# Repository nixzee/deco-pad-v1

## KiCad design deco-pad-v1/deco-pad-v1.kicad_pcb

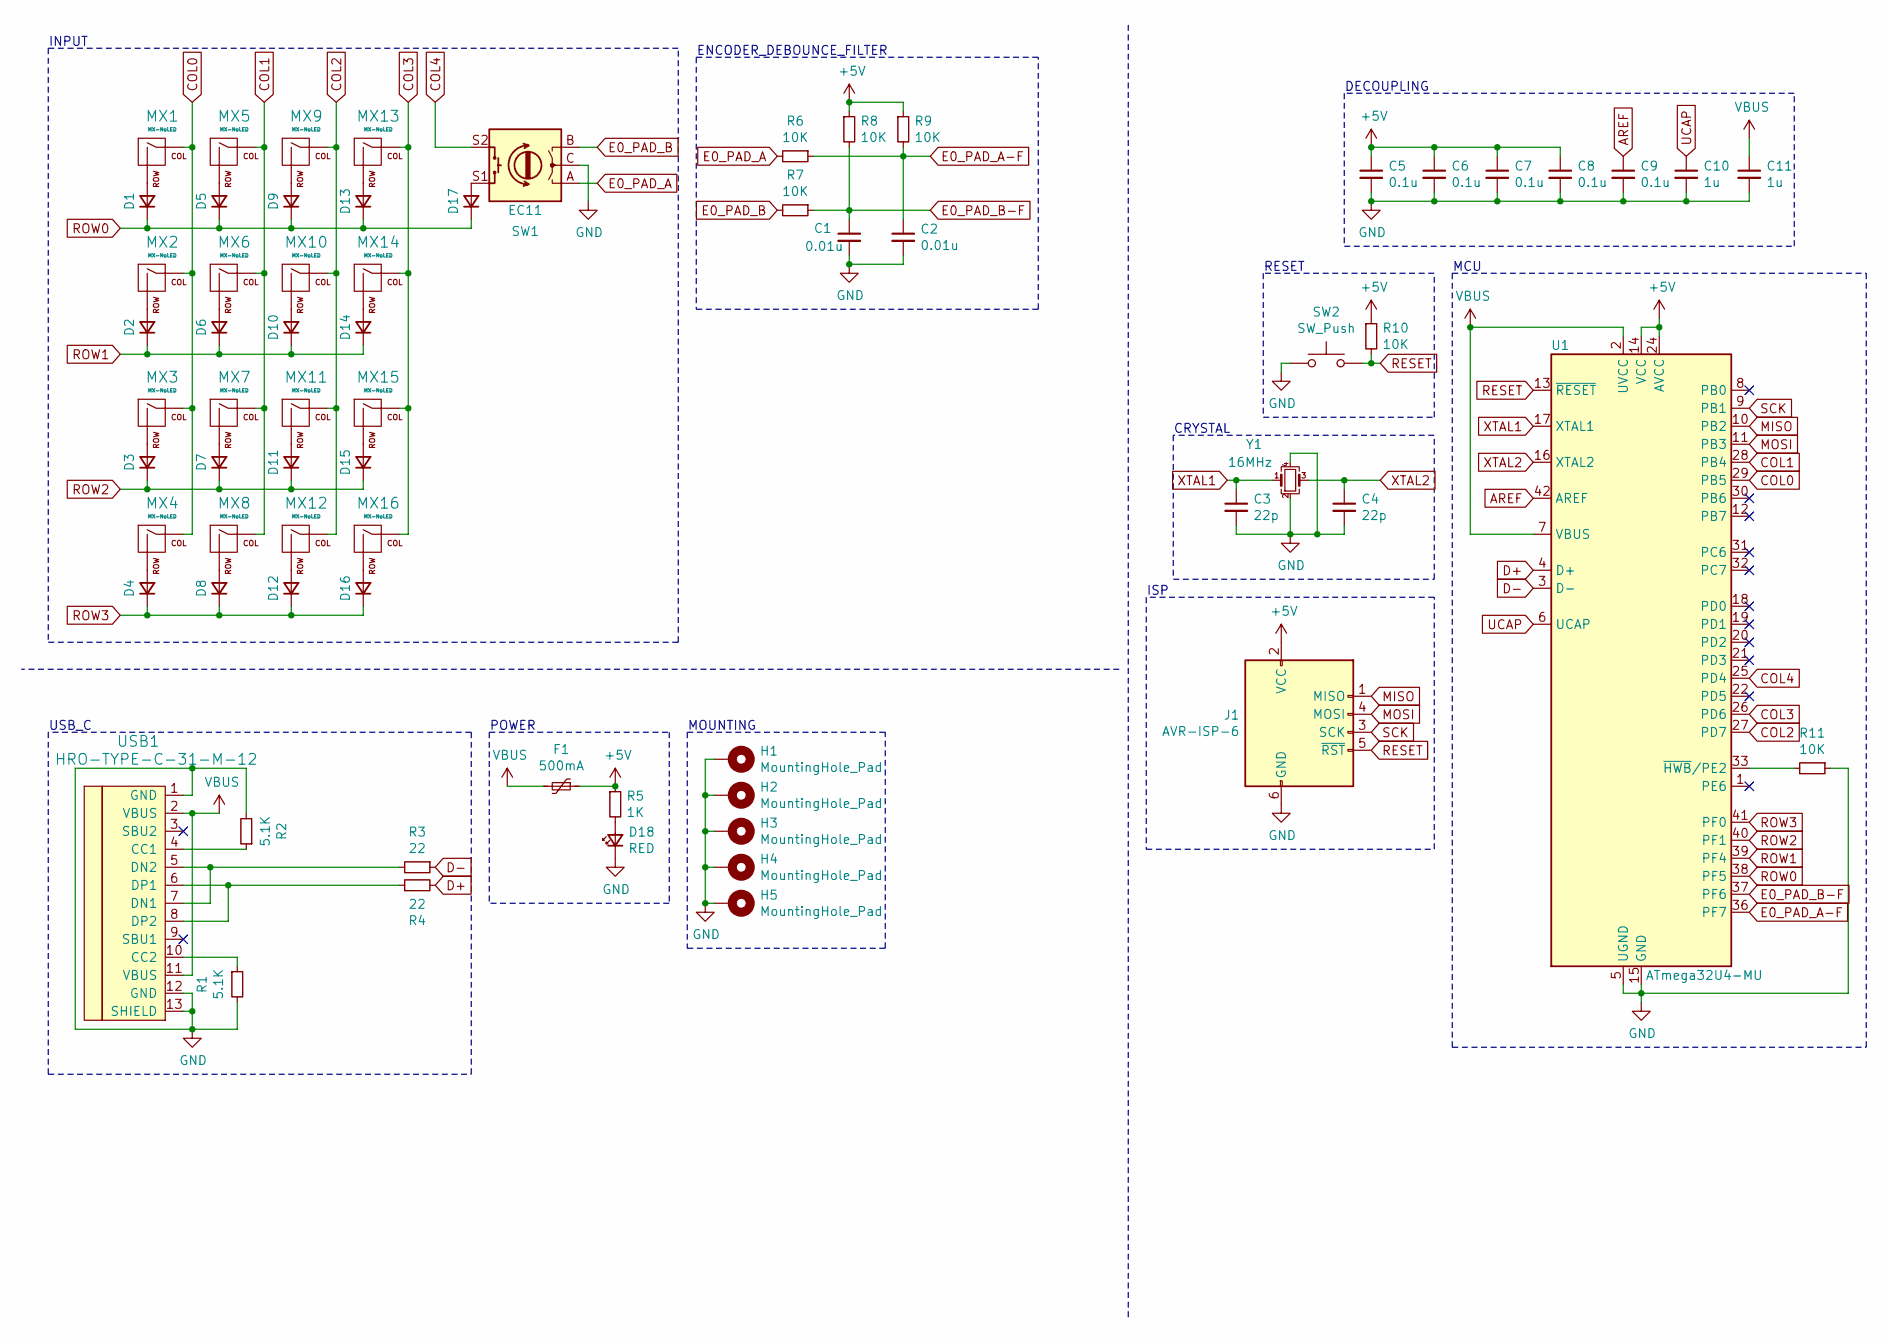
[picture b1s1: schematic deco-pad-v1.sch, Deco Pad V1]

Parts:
C1, C2: 0.01u; C_0805_2012Metric
C3, C4: 22p; C_0805_2012Metric
C5, C6, C7, C8, C9: 0.1u; C_0805_2012Metric
C10, C11: 1u; C_0805_2012Metric
D1, D2, D3, D4, D5, D6, D7, D8, D9, D10, D11, D12, D13, D14, D15, D16, D17: D_Small; D_SOD-123
D18: RED; LED_0805_2012Metric
F1: 500mA; Fuse_1206_3216Metric
H1, H2, H3, H4, H5: MountingHole_Pad; MountingHole_2.2mm_M2_Pad_Via
J1: AVR-ISP-6; PinSocket_2x03_P2.54mm_Vertical
MX1, MX2, MX3, MX4, MX5, MX6, MX7, MX8, MX9, MX10, MX11, MX12, MX13, MX14, MX15, MX16: MX-NoLED; MX-1U-NoLED
R1, R2: 5.1K; R_0805_2012Metric
R3, R4: 22; R_0805_2012Metric
R5: 1K; R_0805_2012Metric
R6, R7, R8, R9, R10, R11: 10K; R_0805_2012Metric
SW1: EC11; RotaryEncoder_Alps_EC11E-Switch_Vertical_H20mm
SW2: SW_Push; SW_SPST_B3S-1000
U1: ATmega32U4-MU; QFN-44-1EP_7x7mm_P0.5mm_EP5.2x5.2mm
USB1: HRO-TYPE-C-31-M-12; HRO-TYPE-C-31-M-12-HandSoldering
Y1: 16MHz; Crystal_SMD_3225-4Pin_3.2x2.5mm

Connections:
+5V: C5.1, C6.1, C7.1, C8.1, F1.1, J1.2 (VCC), R5.1, R8.1, R9.1, R10.1, U1.14 (VCC), U1.24 (AVCC), U1.34 (VCC), U1.44 (AVCC)
AREF: C9.1, U1.42 (AREF)
COL0: MX1.1 (COL), MX2.1 (COL), MX3.1 (COL), MX4.1 (COL), U1.29 (PB5)
COL1: MX5.1 (COL), MX6.1 (COL), MX7.1 (COL), MX8.1 (COL), U1.28 (PB4)
COL2: MX9.1 (COL), MX10.1 (COL), MX11.1 (COL), MX12.1 (COL), U1.27 (PD7)
COL3: MX13.1 (COL), MX14.1 (COL), MX15.1 (COL), MX16.1 (COL), U1.26 (PD6)
COL4: SW1.S2, U1.25 (PD4)
D+: R4.2, U1.4 (D+)
D-: R3.1, U1.3 (D-)
E0_PAD_A: R6.2, SW1.A
E0_PAD_A-F: C2.1, R6.1, R9.2, U1.36 (PF7)
E0_PAD_B: R7.2, SW1.B
E0_PAD_B-F: C1.1, R7.1, R8.2, U1.37 (PF6)
GND: C1.2, C2.2, C3.2, C4.2, C5.2, C6.2, C7.2, C8.2, C9.2, C10.2, C11.2, D18.1 (K), H1.1, H2.1, H3.1, H4.1, H5.1, J1.6 (GND), R1.2, R2.2, R11.1, SW1.C, SW2.1, U1.5 (UGND), U1.15 (GND), U1.23 (GND), U1.35 (GND), U1.43 (GND), U1.45 (GND), USB1.1 (GND), USB1.12 (GND), USB1.13 (SHIELD), Y1.2, Y1.4
MISO: J1.1 (MISO), U1.10 (PB2)
MOSI: J1.4 (MOSI), U1.11 (PB3)
unnamed: D1.2 (A), MX1.2 (ROW)
unnamed: D2.2 (A), MX2.2 (ROW)
unnamed: D3.2 (A), MX3.2 (ROW)
unnamed: D4.2 (A), MX4.2 (ROW)
unnamed: D5.2 (A), MX5.2 (ROW)
unnamed: D6.2 (A), MX6.2 (ROW)
unnamed: D7.2 (A), MX7.2 (ROW)
unnamed: D8.2 (A), MX8.2 (ROW)
unnamed: D9.2 (A), MX9.2 (ROW)
unnamed: D10.2 (A), MX10.2 (ROW)
unnamed: D11.2 (A), MX11.2 (ROW)
unnamed: D12.2 (A), MX12.2 (ROW)
unnamed: D13.2 (A), MX13.2 (ROW)
unnamed: D14.2 (A), MX14.2 (ROW)
unnamed: D15.2 (A), MX15.2 (ROW)
unnamed: D16.2 (A), MX16.2 (ROW)
unnamed: D17.2 (A), SW1.S1
unnamed: D18.2 (A), R5.2
unnamed: R1.1, USB1.10 (CC2)
unnamed: R2.1, USB1.4 (CC1)
unnamed: R3.2, USB1.5 (DN2), USB1.7 (DN1)
unnamed: R4.1, USB1.6 (DP1), USB1.8 (DP2)
unnamed: R11.2, U1.33 (~HWB~/PE2)
RESET: J1.5 (~RST), R10.2, SW2.2, U1.13 (~RESET)
ROW0: D1.1 (K), D5.1 (K), D9.1 (K), D13.1 (K), D17.1 (K), U1.38 (PF5)
ROW1: D2.1 (K), D6.1 (K), D10.1 (K), D14.1 (K), U1.39 (PF4)
ROW2: D3.1 (K), D7.1 (K), D11.1 (K), D15.1 (K), U1.40 (PF1)
ROW3: D4.1 (K), D8.1 (K), D12.1 (K), D16.1 (K), U1.41 (PF0)
SCK: J1.3 (SCK), U1.9 (PB1)
UCAP: C10.1, U1.6 (UCAP)
VBUS: C11.1, F1.2, U1.2 (UVCC), U1.7 (VBUS), USB1.2 (VBUS), USB1.11 (VBUS)
XTAL1: C3.1, U1.17 (XTAL1), Y1.1
XTAL2: C4.1, U1.16 (XTAL2), Y1.3

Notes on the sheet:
MCU
CRYSTAL
ENCODER_DEBOUNCE_FILTER
INPUT
USB_C
RESET
ISP
DECOUPLING
MOUNTING
POWER

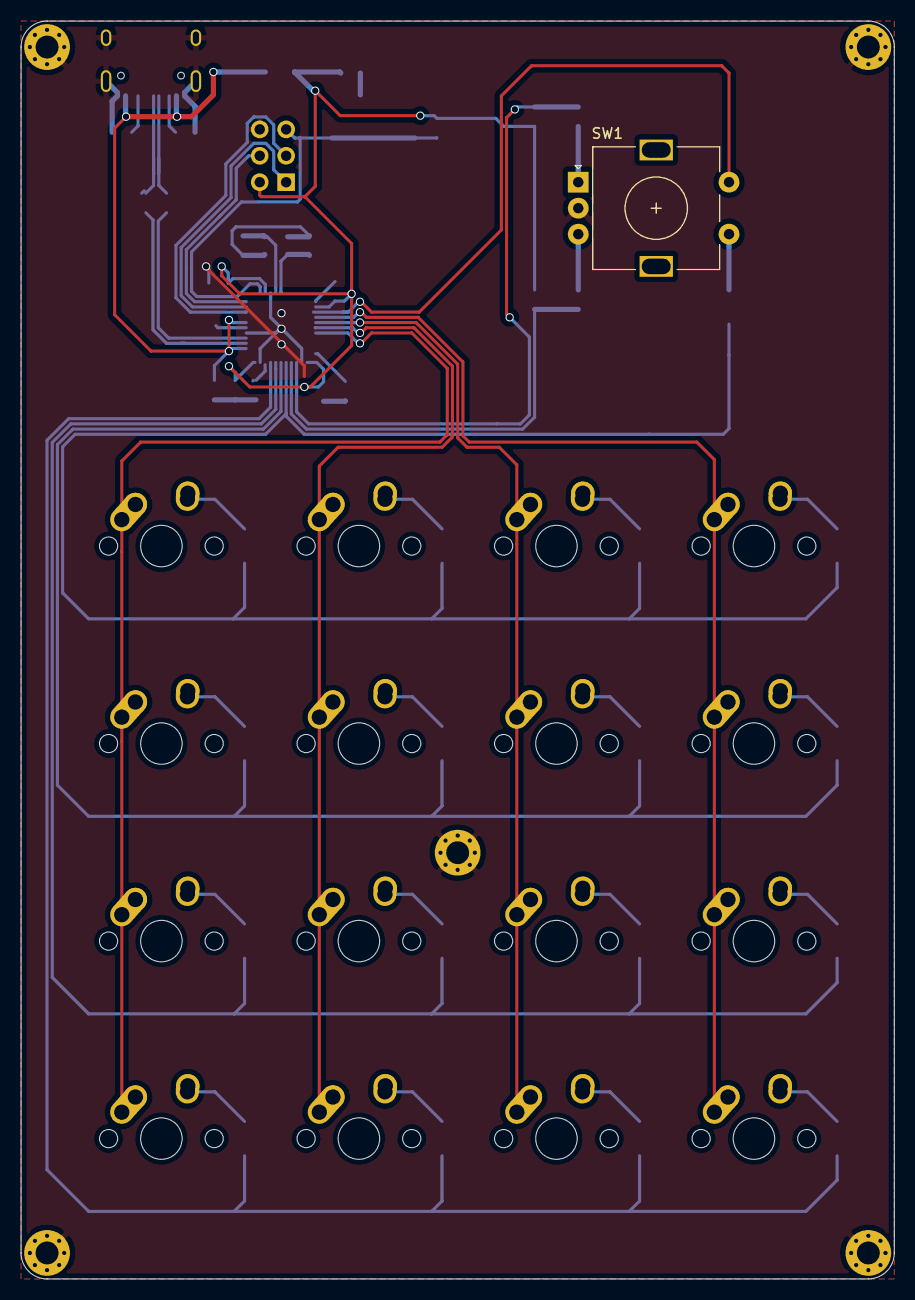
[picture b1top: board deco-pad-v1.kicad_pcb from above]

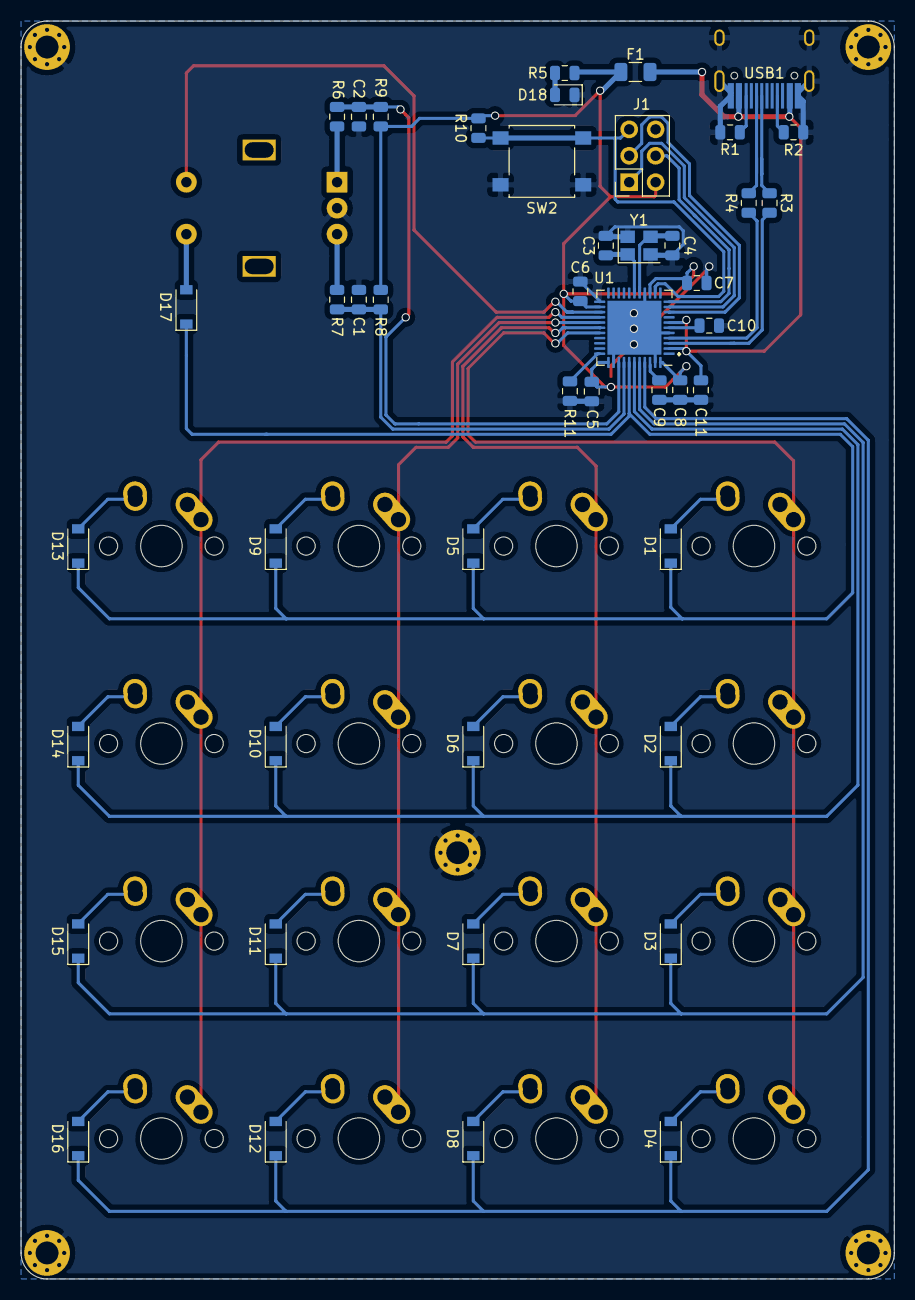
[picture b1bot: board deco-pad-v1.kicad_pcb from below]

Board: 2 copper layers, 84.0 x 121.0 mm, 68 parts (46 on the bottom side), 49 nets.

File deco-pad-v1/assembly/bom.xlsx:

Designator | Package | Quantity | Designation | Part Number | Cost | Total by Board | Total | Link
R5 | R_0805_2012Metric | 1 | 1K | ERA-6AEB102V | 0.33 | 0.33 | 1.6500000000000001 | https://www.digikey.com/product-detail/en/panasonic-electron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
D18 | LED_0805_2012Metric | 1 | RED | LTST-C171KRKT | 0.28000000000000003 | 0.28000000000000003 | 1.4000000000000001 | https://www.digikey.com/product-detail/en/lite-on-inc/LTST-C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
U1 | QFN-44-1EP_7x7mm_P0.5mm_EP5.2x5.2mm | 1 | ATmega32U4-MU | ATMEGA32U4-MU | 3.98 | 3.98 | 19.899999999999999 | https://www.digikey.com/product-detail/en/microchip-technolo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
J1 | PinSocket_2x03_P2.54mm_Vertical | 1 | AVR-ISP-6 | 67997-206HLF | 0.33 | 0.33 | 1.6500000000000001 | https://www.digikey.com/product-detail/en/amphenol-icc-fci/6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
R4,R3 | R_0805_2012Metric | 2 | 22 | ERJ-6GEYJ220V | 0.1 | 0.2 | 1 | https://www.digikey.com/product-detail/en/panasonic-electron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
R9,R8,R7,R6,R11,R10 | R_0805_2012Metric | 6 | 10K | ERA-6AEB103V | 0.33 | 1.98 | 9.9 | https://www.digikey.com/product-detail/en/panasonic-electron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
D17,D16,D15,D14,D13,D12,D11,D10,D9,D8,D7,D6,D5,D4,D3,D2,D1 | D_SOD-123 | 17 | D_Small | 1N4148W-TP | 0.15 | 2.5499999999999998 | 12.75 | https://www.digikey.com/product-detail/en/micro-commercial-c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
C2,C1 | C_0805_2012Metric | 2 | 0.01u | C0805C103J5RAC7210 | 0.1 | 0.2 | 1 | https://www.digikey.com/product-detail/en/kemet/C0805C103J5R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
Y1 | Crystal_SMD_3225-4Pin_3.2x2.5mm | 1 | 16MHz | NX3225SA-16.000M-STD-CSR-1 | 0.75 | 0.75 | 3.75 | https://www.digikey.com/product-detail/en/ndk-america-inc/NX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
USB1 | HRO-TYPE-C-31-M-12-HandSoldering | 1 | HRO-TYPE-C-31-M-12 | HRO-TYPE-C-31-M-12 | 0.99 | 0.99 | 4.95 | https://keeb.io/products/usb-c-port-12-pin-hro-type-c-31-m-12
SW2 | SW_SPST_B3S-1000 | 1 | SW_Push | B3S-1000P | 0.65 | 0.65 | 3.25 | https://www.digikey.com/product-detail/en/omron-electronics-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
SW1 | RotaryEncoder_Alps_EC11E-Switch_Vertical_H20mm | 1 | EC11 | PEC11L-4115F-S0020 | 2.34 | 2.34 | 11.7 | https://www.digikey.com/product-detail/en/bourns-inc/PEC11L-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
R2,R1 | R_0805_2012Metric | 2 | 5.1K | ERA-6AEB512V | 0.33 | 0.66 | 3.3000000000000003 | https://www.digikey.com/product-detail/en/panasonic-electron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
F1 | Fuse_1206_3216Metric | 1 | 500mA | 0ZCJ0050AF2E | 0.19 | 0.19 | 0.95 | https://www.digikey.com/product-detail/en/bel-fuse-inc/0ZCJ0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
C11,C10 | C_0805_2012Metric | 2 | 20 | CL21B105KAFNNNE | 0.1 | 0.2 | 1 | https://www.digikey.com/product-detail/en/samsung-electro-me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
C9,C8,C7,C6,C5 | C_0805_2012Metric | 5 | 0.1u | CL21B104MBCNNNC | 0.1 | 0.5 | 2.5 | https://www.digikey.com/product-detail/en/samsung-electro-me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
C4,C3 | C_0805_2012Metric | 2 | 22p | CL21C220JB61PNC | 0.22 | 0.44 | 2.2000000000000002 | https://www.digikey.com/product-detail/en/samsung-electro-me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
 |  |  |  |  | Total | 16.569999999999997 | 82.850000000000009

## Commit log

2020-07-14 [NZ] Init commit
2020-07-14 [NZ] Starting to add data sheets and cleanup
2020-07-14 [NZ] Added typec and hybrid alps libs (remove for git)
2020-07-14 [NZ] Almost completed on schematic and choosing footprints.
2020-07-15 [NZ] Schematic and Footprints done.
2020-07-15 [NZ] Components are in relative on the pcb layout.
2020-07-15 [NZ] Still staging
2020-07-15 [NZ] PCB ready for review
2020-07-15 [NZ] Cleaned up the schematic.
2020-07-16 [NZ] Adjusted Rotary Encoder.
2020-07-16 [NZ] Added Zip of gerber
2020-07-27 [NZ] Removed ESD while research a backup. Remove schottky since not needed and would drop the voltage too much. Some cleanup. Will add silk art and curved tracks next.
2020-09-09 [NZ] Regenerate gerber and drill file for JCL. Completed BOM and ordered parts.
